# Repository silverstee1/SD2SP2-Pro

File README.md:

The inside PCB must be ordered in 1.2mm thickness. Surface finish must be ENIG at minimum.

The outside PCB must be ordered in 2.0mm thickness.

I recommend https://jlcpcb.com for PCB production.

***Occasionally when receiving the pcb's from JLCPCB the outside pcb may have a bump/not flush cut near the SP1 side when it was cut at the fab and might require sanding to smooth it out for a better fit.***

***Included is a stl cover in the 2.0 project folder that fits flush with the outside pcb***

# SD2SP2 Pro 2.0

SD2SP2 PRO 2.0 BOM
=====================================
The inside PCB must be ordered in 1.2mm thickness. Surface finish must be ENIG at minimum.

The outside PCB must be ordered in 2.0mm thickness.

**Outside PCB**

**C1:** 0402 22u Capactior (10V Min) - DigiKey Part# 490-GRM158R61A226ME15DCT-ND

LCSC Part# C3845593

**J2:** 02x04 2.54mm Female Pin Socket - DigiKey Part# SSW-104-22-F-D-VS-K-TR

LCSC Part# C5160819

**J3:** MicroSD Slot - DigiKey Part# 2223-MSD-4-ACT-ND

LCSC Part# C113206

**U1:** OR Gate IC - DigiKey Part# 296-1093-1-ND

LCSC Part# C7470

Alt Nexperia Digikey Part# 1727-3067-1-ND

LCSC Alt Nexperia Part# C12488

**Inside PCB**

**J1:** 02x04 2.54mm Male Right Angle Pin Header - DigiKey Part# 10129382-908002BLF-ND

LCSC Part# C492432

Special thanks to:
=====================================
 * citrus3000psi for the original project
 * MockyLock for the idea
 * misteraddons for the SD2SP2 PRO  
 * Extrems & emu_kidid for doing the real work needed to make this possible

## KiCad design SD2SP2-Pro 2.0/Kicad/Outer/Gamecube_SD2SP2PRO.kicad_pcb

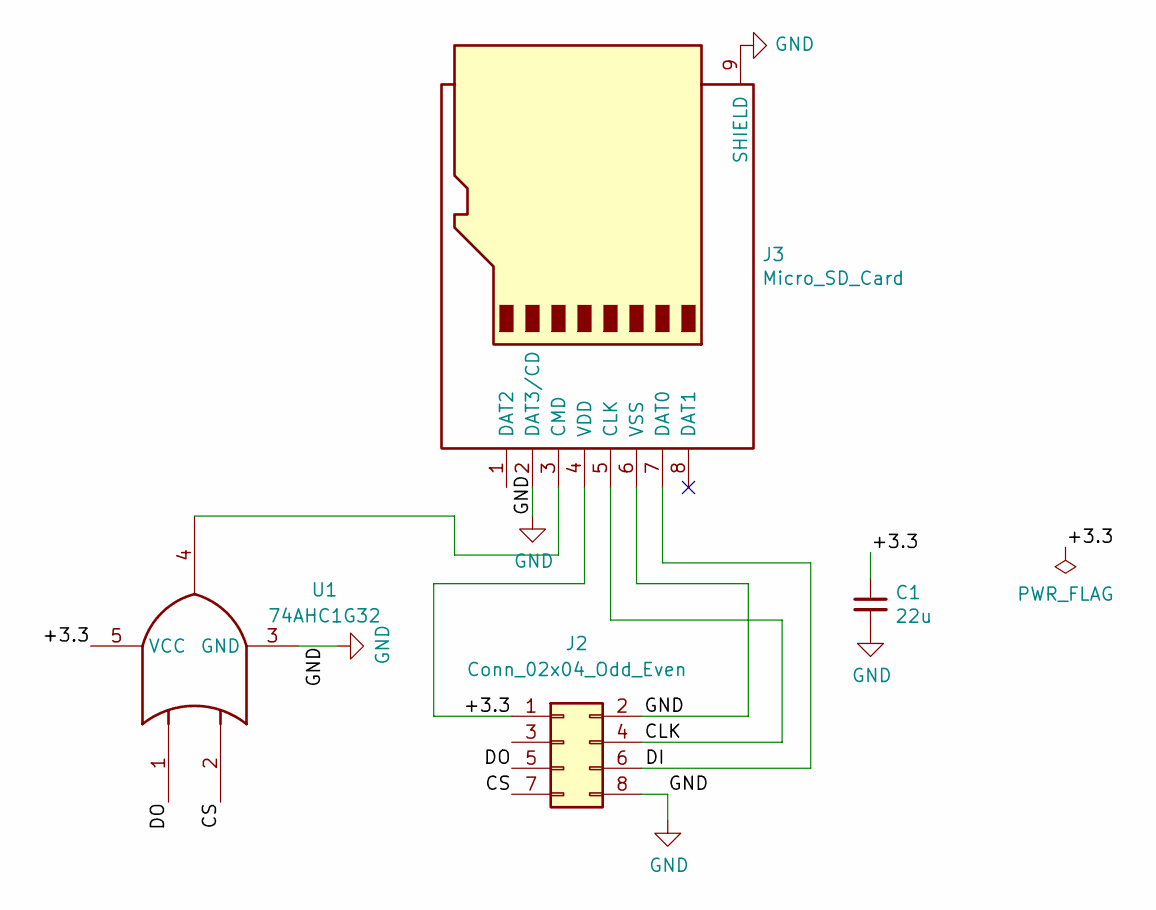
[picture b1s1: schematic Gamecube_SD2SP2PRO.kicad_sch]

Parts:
C1: 22u; C_0402_1005Metric; LCSC Part C1525
J2: Conn_02x04_Odd_Even; PinSocket_2x04_P2.54mm_Vertical_SMD; LCSC Part C5160819
J3: Micro_SD_Card; Micro_SD_C113206; LCSC Part C113206
U1: 74AHC1G32; SC-74A-5_1.55x2.9mm_P0.95mm; LCSC Part C12488

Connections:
/+3.3: C1.1, J2.1, J3.4 (VDD), U1.5 (VCC)
/CLK: J2.4, J3.5 (CLK)
/CS: J2.7, U1.2
/DI: J2.6, J3.7 (DAT0)
/DO: J2.5, U1.1
GND: C1.2, J2.2, J2.8, J3.2 (DAT3/CD), J3.6 (VSS), J3.9 (SHIELD), U1.3 (GND)
unnamed: J3.3 (CMD), U1.4

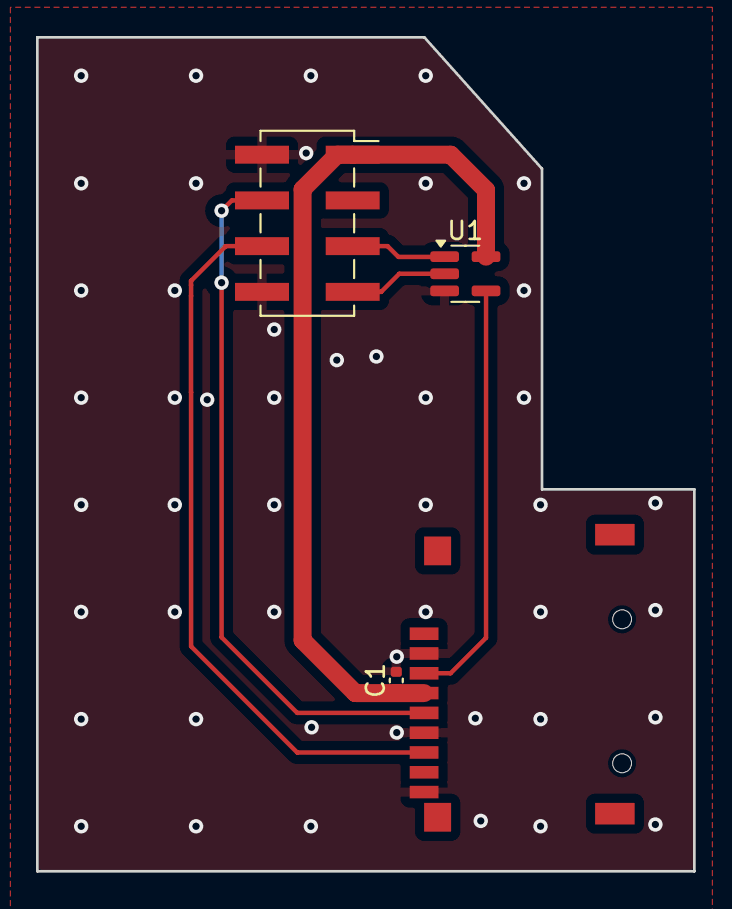
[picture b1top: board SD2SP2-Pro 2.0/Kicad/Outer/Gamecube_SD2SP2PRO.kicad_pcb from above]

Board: 2 copper layers, 36.5 x 46.3 mm, 4 parts (0 on the bottom side), 7 nets.

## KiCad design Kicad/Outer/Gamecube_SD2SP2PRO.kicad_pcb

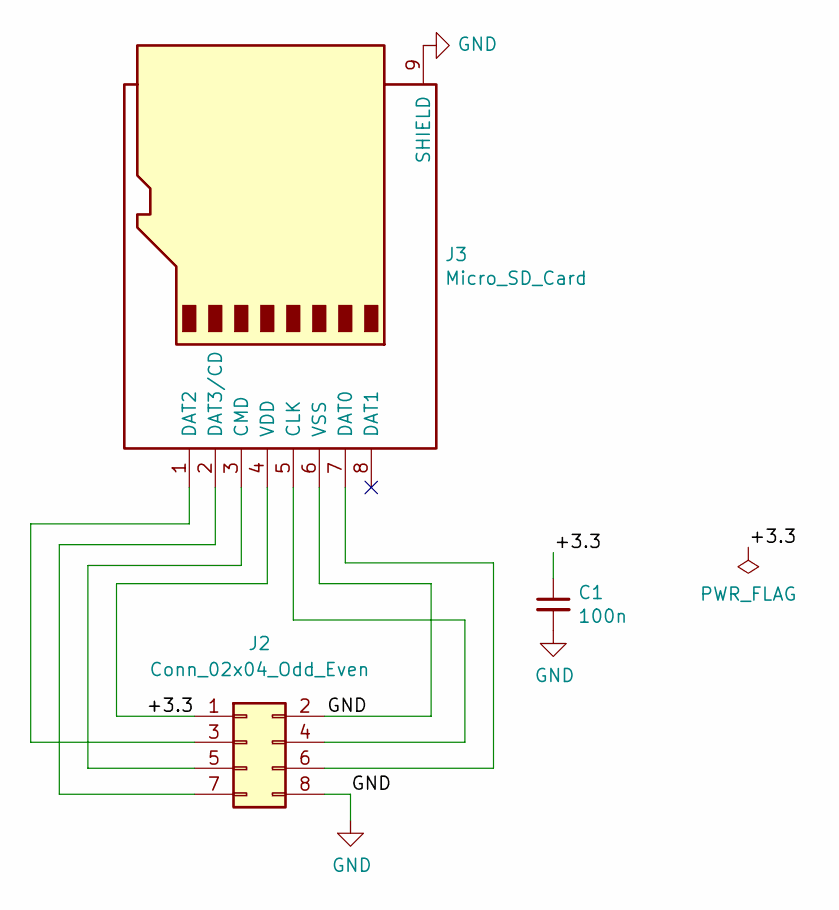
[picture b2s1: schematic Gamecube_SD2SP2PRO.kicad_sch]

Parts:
C1: 100n; C_0402_1005Metric; LCSC Part C1525
J2: Conn_02x04_Odd_Even; PinSocket_2x04_P2.54mm_Vertical_SMD; LCSC Part C5160819
J3: Micro_SD_Card; Micro_SD_C113206; LCSC Part C113206

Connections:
/+3.3: C1.1, J2.1, J3.4 (VDD)
GND: C1.2, J2.2, J2.8, J3.6 (VSS), J3.9 (SHIELD)
unnamed: J2.3, J3.1 (DAT2)
unnamed: J2.4, J3.5 (CLK)
unnamed: J2.5, J3.3 (CMD)
unnamed: J2.6, J3.7 (DAT0)
unnamed: J2.7, J3.2 (DAT3/CD)

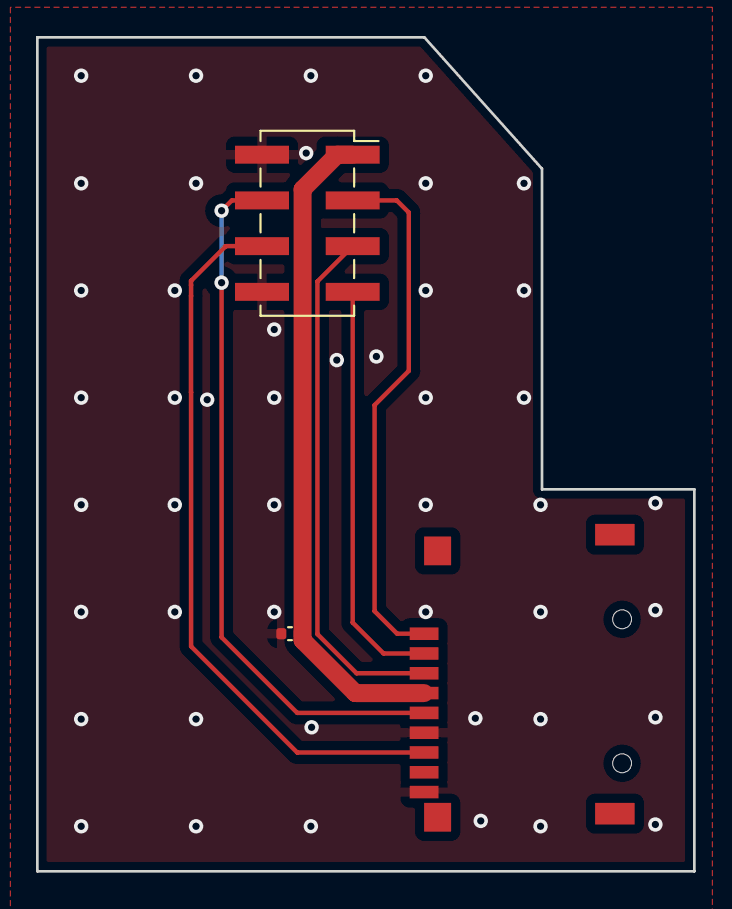
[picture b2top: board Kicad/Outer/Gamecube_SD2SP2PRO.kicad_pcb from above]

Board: 2 copper layers, 36.5 x 46.3 mm, 3 parts (0 on the bottom side), 7 nets.

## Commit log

2023-02-12 renamed file
2023-02-12 new pics
2024-06-28 updated SD2SP2 Pro 2.0
    added pcb gerbers and updated project files in separate SD2SP2-Pro 2.0 folder
2024-06-28 Outer PCB changes
    fixed silkscreen for C1 and moved C1 closer to MicroSD Slot
2024-06-28 Outer Board C1 Silkscreen and relocation
    Moved C1 closer to MicroSD slot and fixed C1 Silkscreen layer
2024-06-28 updated schematic
2024-06-28 added LCSC alt part#
2025-06-08 add SP2 port cover
    remixed from Jeff Chen's port cover
2025-06-08 Update README.md
    spelling errors and removed v1 pics to avoid confusion on V2.0
